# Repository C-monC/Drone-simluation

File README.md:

# Drone-simluation

Experimenting with reinforcement learning for drone control. 

KICAD schematics in drone_controller folder.
OpenAI gym environment in gym_multirotor folder.

## Installation

Install mujuco:
https://github.com/google-deepmind/mujoco (Download latest release and extract in ~/.mujoco/)

Install packages:
```
pip install -r requirements.txt
```
Run main to train the hovering agent.
```
python main.py
```

TODO simulation:
- [ ] Add sensor/reward information in Mujoco interface when rendering
- [ ] Add noise to sensor information
- [ ] Add noise (wind, etc.) to simulation
- [ ] Model GPS, IMU, Compass sensor in Env

TODO Drone:
- [ ] Route PCB
- [ ] Firmware

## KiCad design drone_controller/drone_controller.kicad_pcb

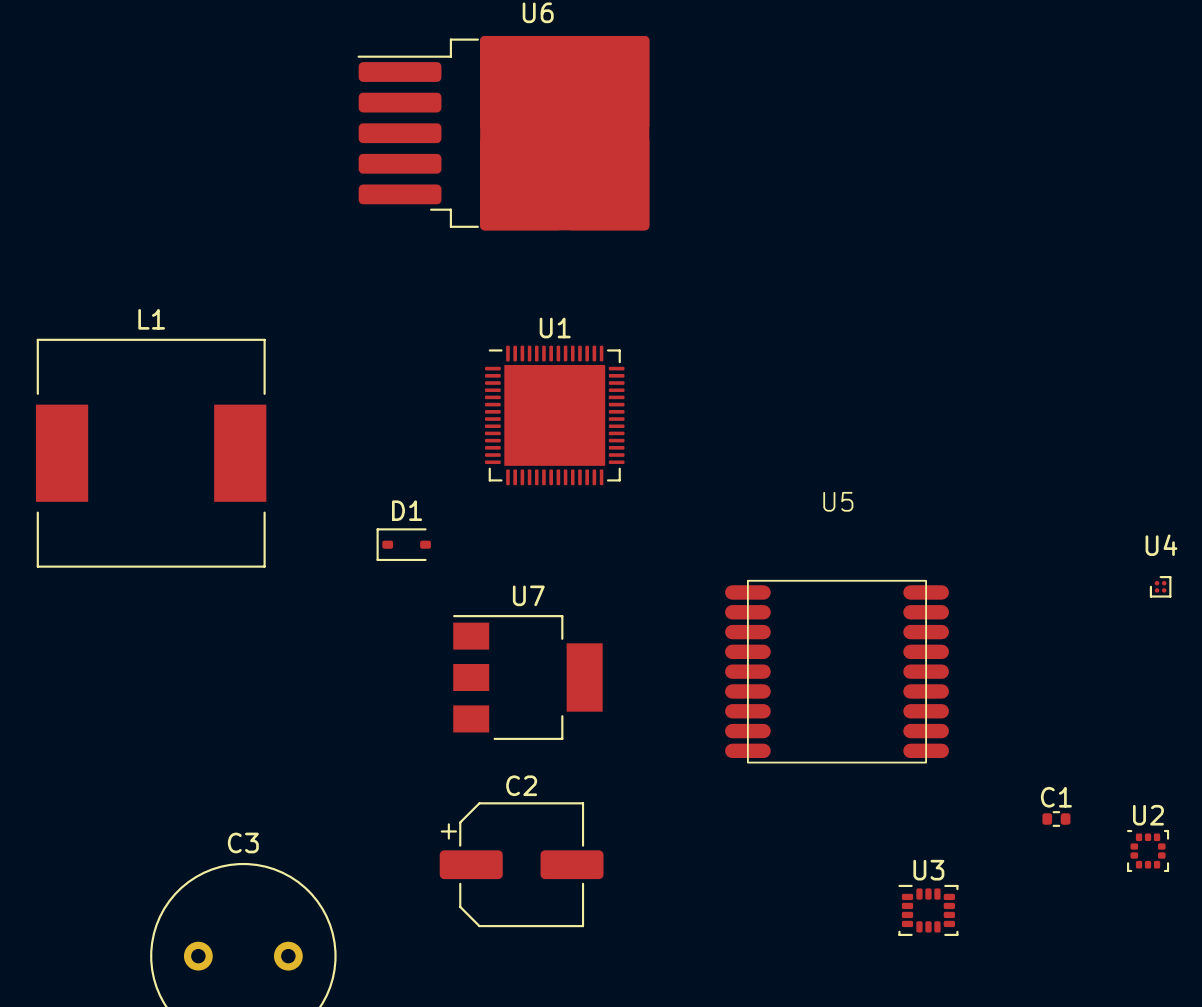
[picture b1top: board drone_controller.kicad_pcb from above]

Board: 2 copper layers, 12 parts (0 on the bottom side), 11 nets, no tracks yet.

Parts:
C1: 100nFC; R_0402_1005Metric
C2: 220uFC; CP_Elec_6.3x5.4
C3: 680uFC; C_Radial_D10.0mm_H16.0mm_P5.00mm
D1: 1N5819WS; D_SOD-323
L1: 33uHL; L_12x12mm_H8mm
U1: ESP32-S3; QFN-56-1EP_7x7mm_P0.4mm_EP5.6x5.6mm
U2: LPS22HH; ST_HLGA-10_2x2mm_P0.5mm_LayoutBorder3x2y
U3: LSM6DS3; LGA-14_3x2.5mm_P0.5mm_LayoutBorder3x4y
U4: MMC5633NJL; WLP-4_0.86x0.86mm_P0.4mm
U5: SW-GPS01
U6: LM2596S-5; TO-263-5_TabPin3
U7: AMS1117-3.3; SOT-223-3_TabPin2

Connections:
+3V3: U5.7 (VCC_IO), U5.8 (VCC), U7.2 (VO)
+5V: C2.1, L1.2, U6.4 (FB), U7.3 (VI)
+BATT: C1.2, C3.1, U2.1 (Vdd_IO), U2.10 (VDD), U6.1 (VIN)
-BATT: C1.1, C2.2, C3.2, D1.2 (A), U5.1 (GND1), U5.10 (GND2), U5.12 (GND3), U6.3 (GND), U6.5 (~ON/OFF), U7.1 (GND)
unnamed: D1.1 (K), L1.1, U6.2 (OUT)
unnamed: U1.50 (U0RXD/PROG/GPIO44), U5.3 (RXD)
unnamed: U1.49 (U0TXD/PROG/GPIO43), U5.2 (TXD)
unnamed: U1.55 (VDDA), U1.56 (VDDA)
unnamed: U2.8 (GND), U2.9 (GND)
unnamed: U3.6 (GND), U3.7 (GND)
VDD3P3: U1.2 (VDD3P3), U1.3 (VDD3P3)

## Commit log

2023-10-15 add simulation env
2023-10-15 add info to readme
2023-10-15 Upgrade to gymnasium and mujoco 2.3
2023-10-15 More updates to get gymnasium working
2023-10-15 fix bug in model simulation
2023-10-15 Add some vleis to the README
